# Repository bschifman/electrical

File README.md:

# electrical
We make electricity

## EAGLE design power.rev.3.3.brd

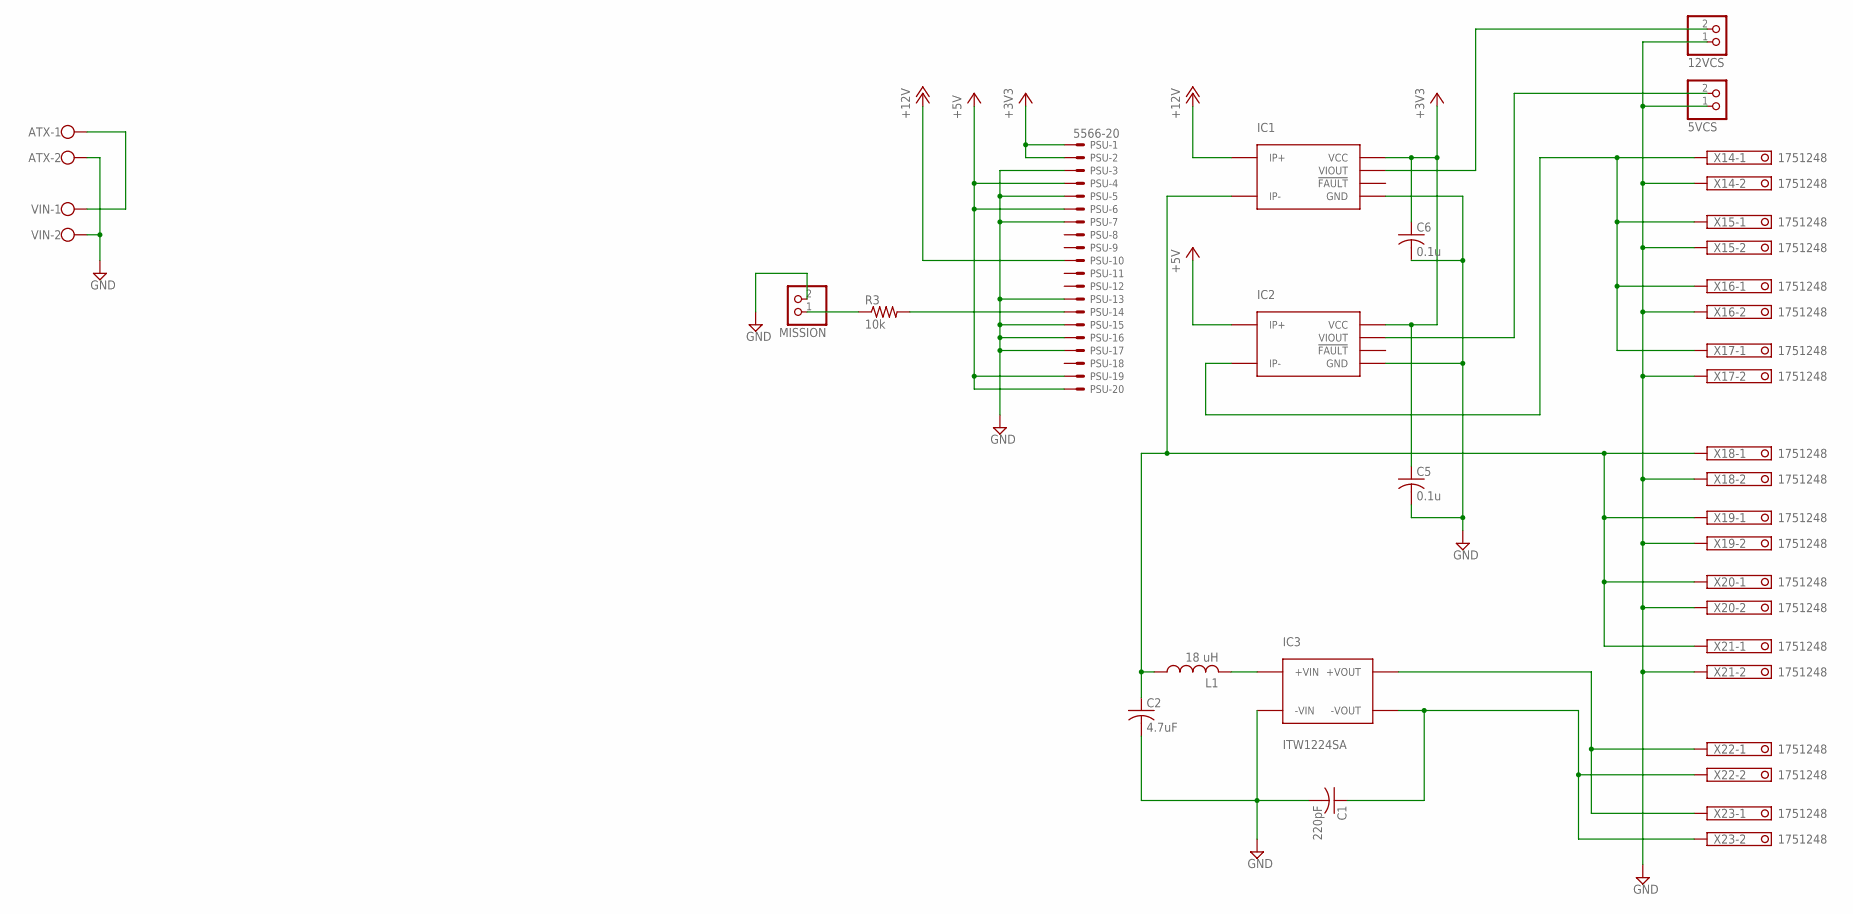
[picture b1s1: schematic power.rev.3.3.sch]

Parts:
5VCS, 12VCS: PINHD-1X2; 1X02
ATX: W237-102
C1: 220pF; C1206
C2: 4.7uF; C1206
C5, C6: 0.1u; C0805
IC1, IC2: ACS711; 12-WFQFN
IC3: ITW1224SA; 6-SIP
L1: 18 uH; L2825P
MISSION: PINHD-1X2; 1X02
PSU: 5566-20
R3: 10k; R0805
VIN: W237-102
X14, X15, X16, X17, X18, X19, X20, X21, X22, X23: 1751248

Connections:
+3V3: C5.1, C6.1, IC1.P$10 (VCC), IC2.P$10 (VCC), PSU.1, PSU.2
+5V: IC2.P$1 (IP+), PSU.4, PSU.6, PSU.19, PSU.20
+12V: IC1.P$1 (IP+), PSU.10
GND: 5VCS.1, 12VCS.1, ATX.2, C1.2, C2.2, C5.2, C6.2, IC1.P$3 (GND), IC2.P$3 (GND), IC3.P$1 (-VIN), MISSION.2, PSU.3, PSU.5, PSU.7, PSU.13, PSU.15, PSU.16, PSU.17, VIN.2, X14.2, X15.2, X16.2, X17.2, X18.2, X19.2, X20.2, X21.2
unnamed: IC3.P$3 (+VOUT), X22.1, X23.1
unnamed: C1.1, IC3.P$5 (-VOUT), X22.2, X23.2
unnamed: IC3.P$2 (+VIN), L1.2
unnamed: ATX.1, VIN.1
unnamed: PSU.14, R3.2
unnamed: MISSION.1, R3.1
unnamed: C2.1, IC1.P$2 (IP-), L1.1, X18.1, X19.1, X20.1, X21.1
unnamed: IC2.P$2 (IP-), X14.1, X15.1, X16.1, X17.1
unnamed: 12VCS.2, IC1.P$9 (VIOUT)
unnamed: 5VCS.2, IC2.P$9 (VIOUT)

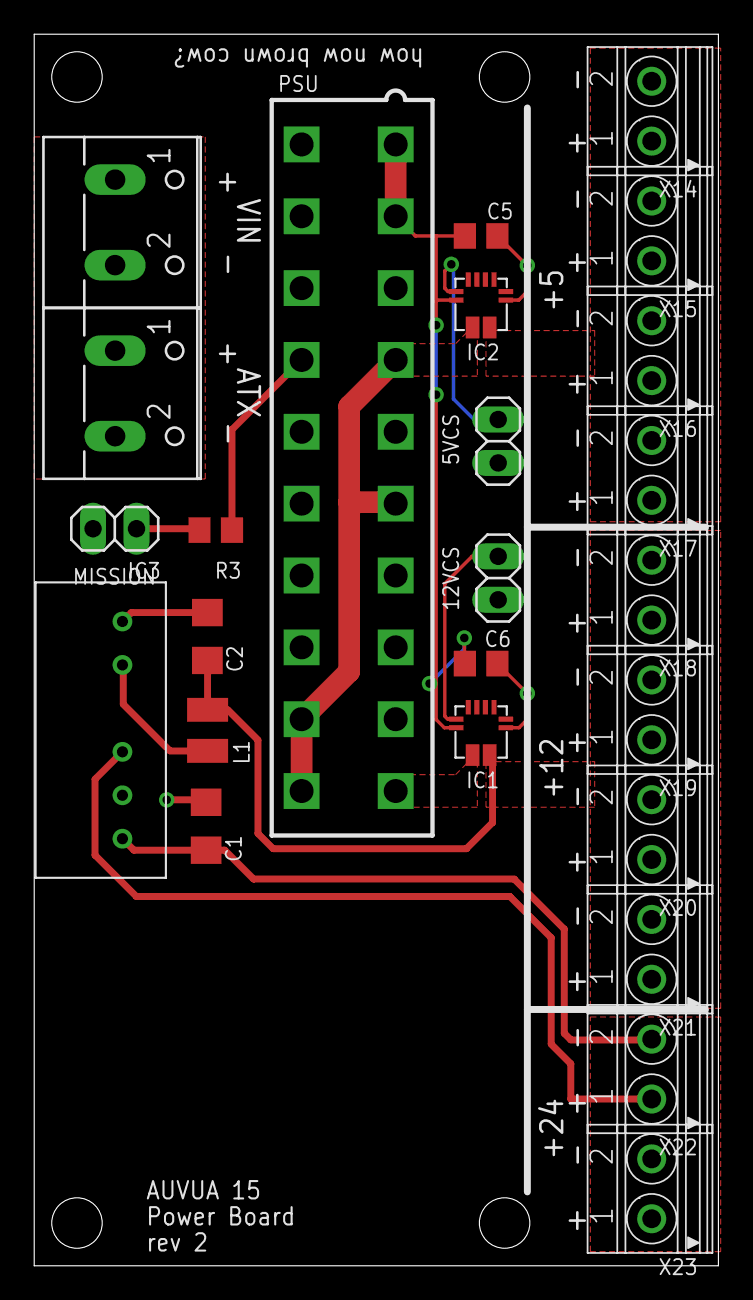
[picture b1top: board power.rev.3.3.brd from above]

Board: 2 copper layers, 40.0 x 72.0 mm, 25 parts (0 on the bottom side), 14 nets.

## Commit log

2016-02-20 Added files via upload
    Power Board Rev 3.3 & 3.4
2016-03-28 Added Altium actuators board files
2016-03-28 test
